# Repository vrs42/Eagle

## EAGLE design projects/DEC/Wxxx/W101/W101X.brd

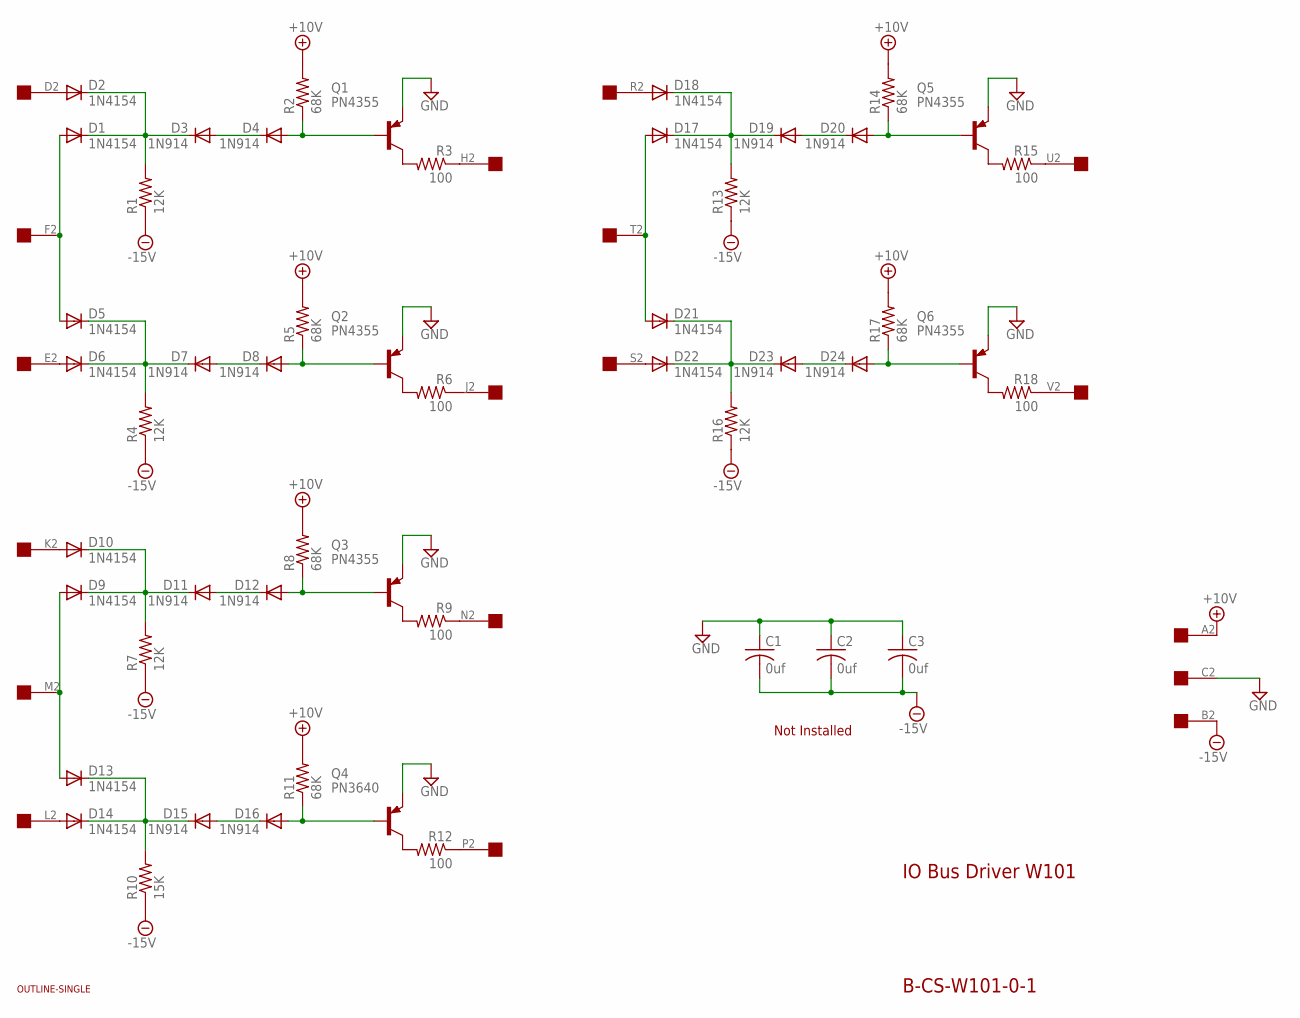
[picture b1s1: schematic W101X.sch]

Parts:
C1, C2, C3: 0uf; C050-025X075
D1, D2, D5, D6, D9, D10, D13, D14, D17, D18, D21, D22: 1N4154; DO35-10
D3, D4, D7, D8, D11, D12, D15, D16, D19, D20, D23, D24: 1N914; DO35-10
Q1, Q2, Q3, Q5, Q6: PN4355; TO39
Q4: PN3640; TO39
R1, R4, R7, R13, R16: 12K; 0207/10
R2, R5, R8, R11, R14, R17: 68K; 0207/10
R3, R6, R9, R12, R15, R18: 100; 0207/10
R10: 15K; 0207/10
U$1: OUTLINE-SINGLE; SINGLE
U$2: EDGE-1; EDGE-CON1

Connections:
+10V: R2.2, R5.2, R8.2, R11.2, R14.2, R17.2, U$2.A2
-15V: C1.2, C2.2, C3.2, R1.1, R4.1, R7.1, R10.1, R13.1, R16.1, U$2.B2
GND: C1.1, C2.1, C3.1, Q1.1 (E), Q2.1 (E), Q3.1 (E), Q4.1 (E), Q5.1 (E), Q6.1 (E), U$2.C2
unnamed: D2.A, U$2.D2
unnamed: D8.A, Q2.2 (B), R5.1
unnamed: R3.1, U$2.H2
unnamed: Q2.3 (C), R6.2
unnamed: D6.A, U$2.E2
unnamed: D5.C, D6.C, D7.C, R4.2
unnamed: D7.A, D8.C
unnamed: D12.A, Q3.2 (B), R8.1
unnamed: Q3.3 (C), R9.2
unnamed: D9.A, D13.A, U$2.M2
unnamed: D9.C, D10.C, D11.C, R7.2
unnamed: D11.A, D12.C
unnamed: R6.1, U$2.J2
unnamed: D10.A, U$2.K2
unnamed: R9.1, U$2.N2
unnamed: R12.1, U$2.P2
unnamed: D18.A, U$2.R2
unnamed: R15.1, U$2.U2
unnamed: D4.A, Q1.2 (B), R2.1
unnamed: Q1.3 (C), R3.2
unnamed: D1.A, D5.A, U$2.F2
unnamed: D1.C, D2.C, D3.C, R1.2
unnamed: D3.A, D4.C
unnamed: D16.A, Q4.2 (B), R11.1
unnamed: Q4.3 (C), R12.2
unnamed: D14.A, U$2.L2
unnamed: D13.C, D14.C, D15.C, R10.2
unnamed: D15.A, D16.C
unnamed: D20.A, Q5.2 (B), R14.1
unnamed: Q5.3 (C), R15.2
unnamed: D17.A, D21.A, U$2.T2
unnamed: D17.C, D18.C, D19.C, R13.2
unnamed: D19.A, D20.C
unnamed: D24.A, Q6.2 (B), R17.1
unnamed: Q6.3 (C), R18.2
unnamed: D22.A, U$2.S2
unnamed: D21.C, D22.C, D23.C, R16.2
unnamed: D23.A, D24.C
unnamed: R18.1, U$2.V2

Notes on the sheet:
IO Bus Driver W101
B-CS-W101-0-1
Not Installed

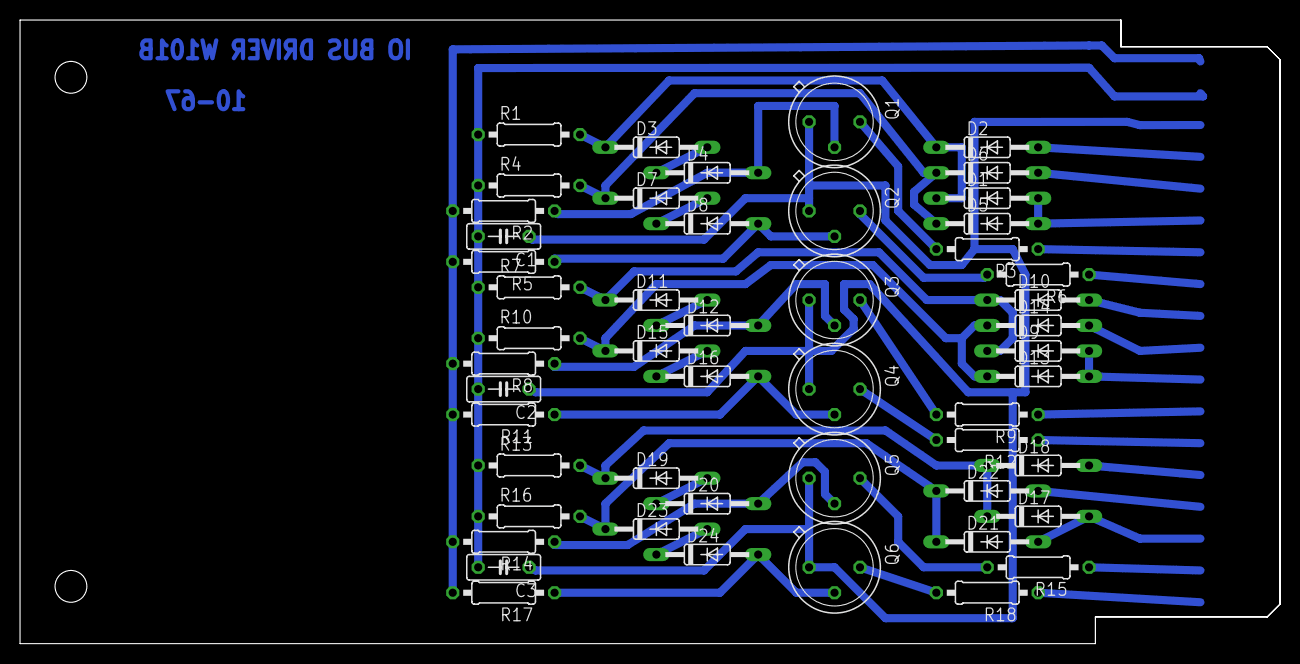
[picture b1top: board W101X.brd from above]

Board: 2 copper layers, 125.7 x 62.2 mm, 53 parts (0 on the bottom side), 42 nets.

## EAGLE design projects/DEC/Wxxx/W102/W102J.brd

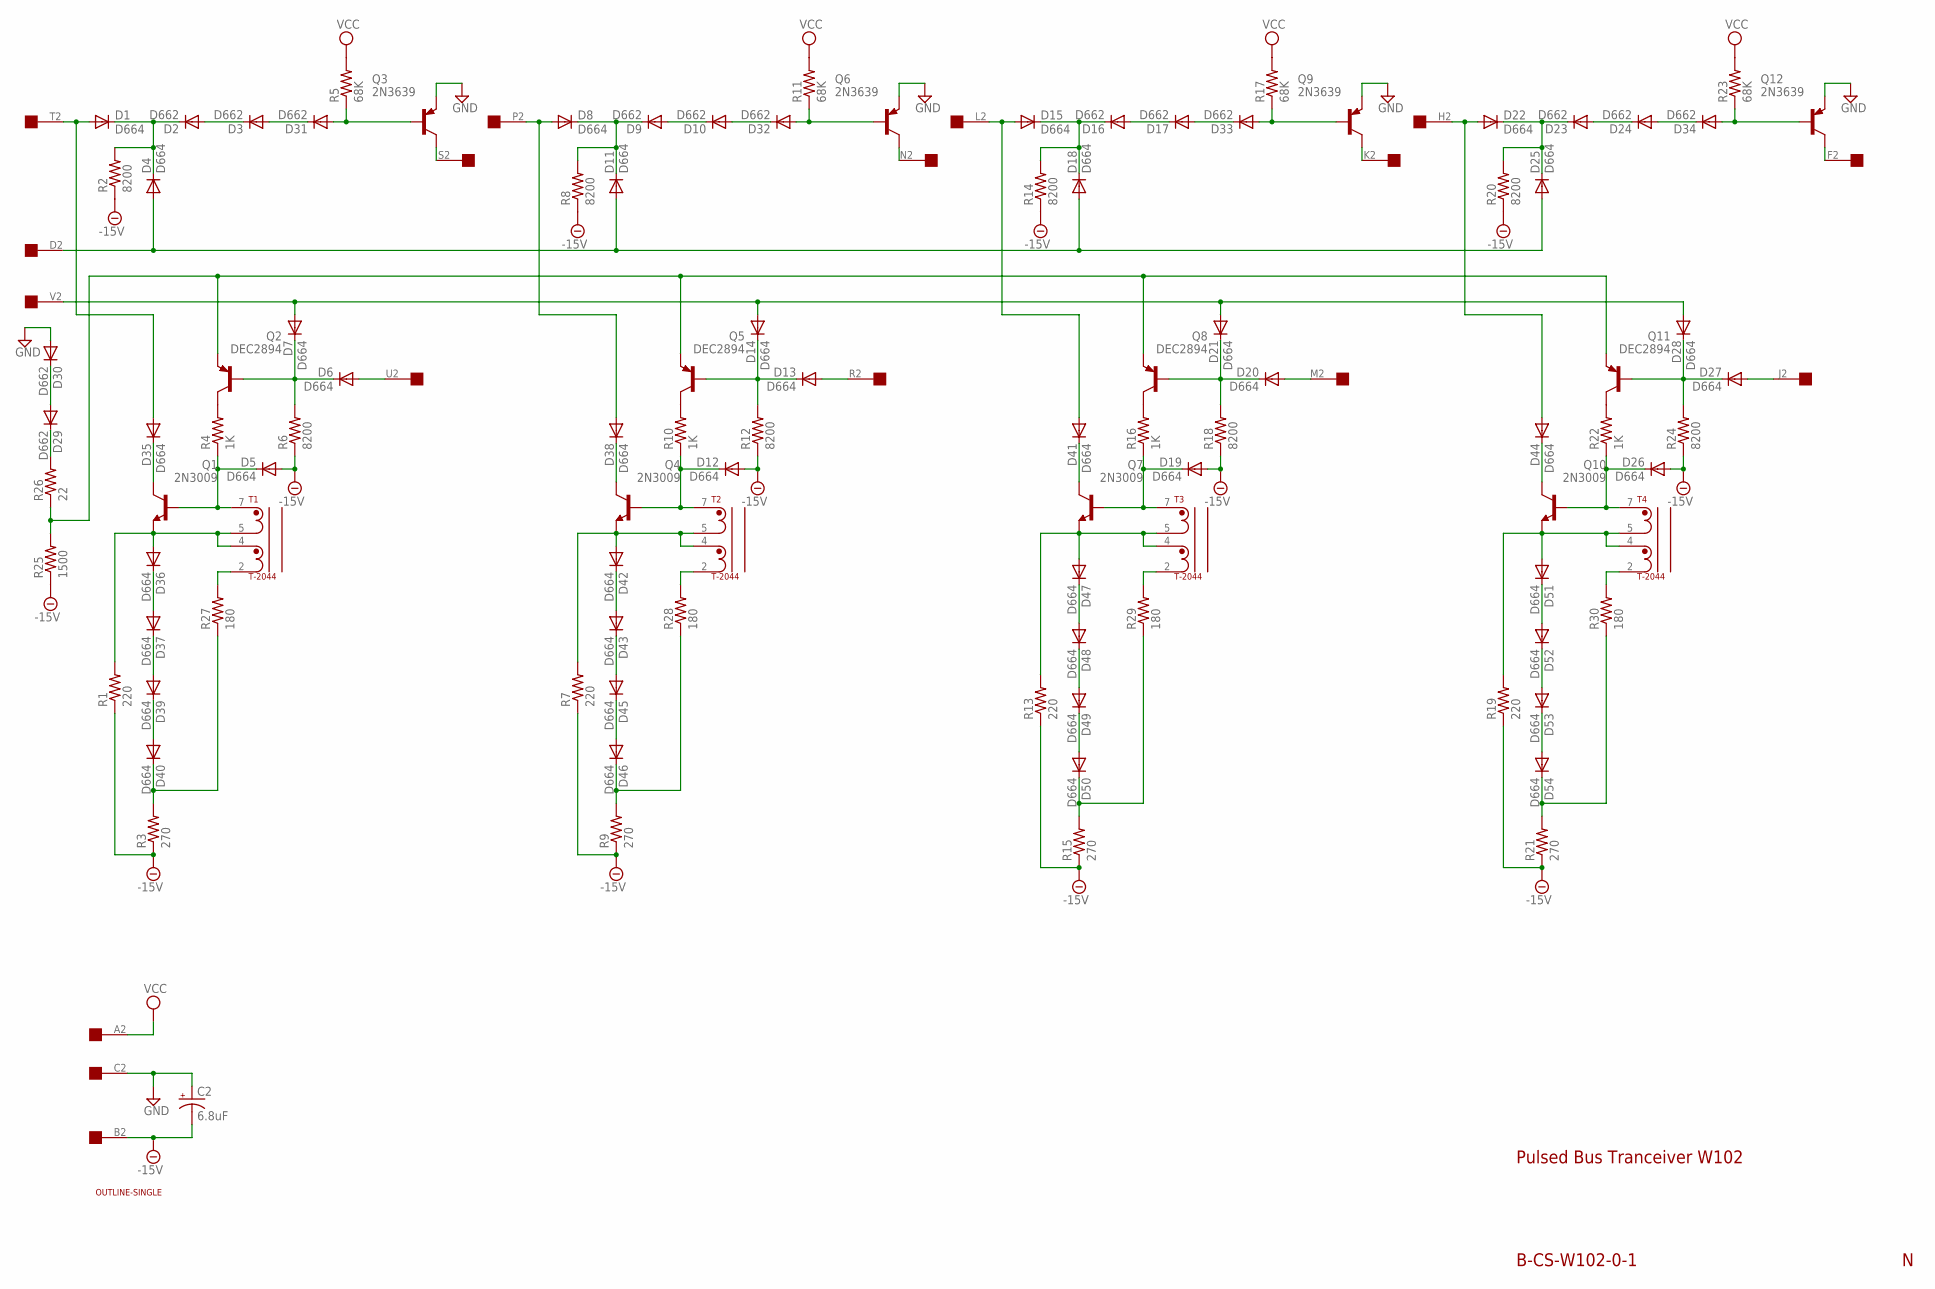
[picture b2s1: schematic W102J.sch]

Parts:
C2: 6.8uF; E15-5
D1, D4, D5, D6, D7, D8, D11, D12, D13, D14, D15, D18, D19, D20, D21, D22, D25, D26, D27, D28, D35, D36, D37, D38, D39, D40, D41, D42, D43, D44, D45, D46, D47, D48, D49, D50, D51, D52, D53, D54: D664; DO35-10
D2, D3, D9, D10, D16, D17, D23, D24, D29, D30, D31, D32, D33, D34: D662; DO35-10
Q1, Q4, Q7, Q10: 2N3009; TO5
Q2, Q5, Q8, Q11: DEC2894; TO5
Q3, Q6, Q9, Q12: 2N3639; TO5
R1, R7, R13, R19: 220; 0207/10
R2, R6, R8, R12, R14, R18, R20, R24: 8200; 0207/10
R3, R9, R15, R21: 270; 0207/10
R4, R10, R16, R22: 1K; 0207/10
R5, R11, R17, R23: 68K; 0207/10
R25: 1500; 0207/10
R26: 22; 0207/10
R27, R28, R29, R30: 180; 0207/10
T1, T2, T3, T4: T-2044; TRANSFORMER
U$1: OUTLINE-SINGLE; SINGLE
U$2: EDGE-1; EDGE-CON1

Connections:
-15V: C2.-, D5.A, D12.A, D19.A, D26.A, R1.1, R2.1, R3.1, R6.1, R7.1, R8.1, R9.1, R12.1, R13.1, R14.1, R15.1, R18.1, R19.1, R20.1, R21.1, R24.1, R25.1, U$2.B2
D2: D4.A, D11.A, D18.A, D25.A, U$2.D2
F2: Q12.3 (C), U$2.F2
GND: C2.+, D30.A, Q3.1 (E), Q6.1 (E), Q9.1 (E), Q12.1 (E), U$2.C2
H2: D22.A, D44.A, U$2.H2
J2: D27.A, U$2.J2
K2: Q9.3 (C), U$2.K2
L2: D15.A, D41.A, U$2.L2
M2: D20.A, U$2.M2
N2: Q6.3 (C), U$2.N2
unnamed: D1.C, D2.C, D4.C, R2.2
unnamed: D2.A, D3.C
unnamed: D3.A, D31.C
unnamed: D6.C, D7.C, Q2.2 (B), R6.2
unnamed: D8.C, D9.C, D11.C, R8.2
unnamed: D9.A, D10.C
unnamed: D10.A, D32.C
unnamed: D13.C, D14.C, Q5.2 (B), R12.2
unnamed: D15.C, D16.C, D18.C, R14.2
unnamed: D16.A, D17.C
unnamed: D17.A, D33.C
unnamed: D20.C, D21.C, Q8.2 (B), R18.2
unnamed: D22.C, D23.C, D25.C, R20.2
unnamed: D23.A, D24.C
unnamed: D24.A, D34.C
unnamed: D27.C, D28.C, Q11.2 (B), R24.2
unnamed: D5.C, Q1.2 (B), R4.1, T1.7 (2)
unnamed: D12.C, Q4.2 (B), R10.1, T2.7 (2)
unnamed: D19.C, Q7.2 (B), R16.1, T3.7 (2)
unnamed: D26.C, Q10.2 (B), R22.1, T4.7 (2)
unnamed: Q2.3 (C), R4.2
unnamed: Q8.3 (C), R16.2
unnamed: D36.A, Q1.1 (E), R1.2, T1.4 (1), T1.5
unnamed: D42.A, Q4.1 (E), R7.2, T2.4 (1), T2.5
unnamed: D47.A, Q7.1 (E), R13.2, T3.4 (1), T3.5
unnamed: D51.A, Q10.1 (E), R19.2, T4.4 (1), T4.5
unnamed: D35.C, Q1.3 (C)
unnamed: D39.C, D40.A
unnamed: D37.C, D39.A
unnamed: D36.C, D37.A
unnamed: R27.2, T1.2 (6)
unnamed: D40.C, R3.2, R27.1
unnamed: D31.A, Q3.2 (B), R5.1
unnamed: D42.C, D43.A
unnamed: D38.C, Q4.3 (C)
unnamed: D43.C, D45.A
unnamed: D32.A, Q6.2 (B), R11.1
unnamed: D33.A, Q9.2 (B), R17.1
unnamed: D34.A, Q12.2 (B), R23.1
unnamed: D45.C, D46.A
unnamed: Q2.1 (E), Q5.1 (E), Q8.1 (E), Q11.1 (E), R25.2, R26.1
unnamed: D29.C, R26.2
unnamed: D29.A, D30.C
unnamed: Q11.3 (C), R22.2
unnamed: Q5.3 (C), R10.2
unnamed: R28.2, T2.2 (6)
unnamed: D41.C, Q7.3 (C)
unnamed: D47.C, D48.A
unnamed: D48.C, D49.A
unnamed: D49.C, D50.A
unnamed: R29.2, T3.2 (6)
unnamed: D46.C, R9.2, R28.1
unnamed: D44.C, Q10.3 (C)
unnamed: D53.C, D54.A
unnamed: D50.C, R15.2, R29.1
unnamed: D52.C, D53.A
unnamed: D51.C, D52.A
unnamed: R30.2, T4.2 (6)
unnamed: D54.C, R21.2, R30.1
P2: D8.A, D38.A, U$2.P2
R2: D13.A, U$2.R2
S2: Q3.3 (C), U$2.S2
T2: D1.A, D35.A, U$2.T2
U2: D6.A, U$2.U2
V2: D7.A, D14.A, D21.A, D28.A, U$2.V2
VCC: R5.2, R11.2, R17.2, R23.2, U$2.A2

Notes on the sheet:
Pulsed Bus Tranceiver W102
B-CS-W102-0-1

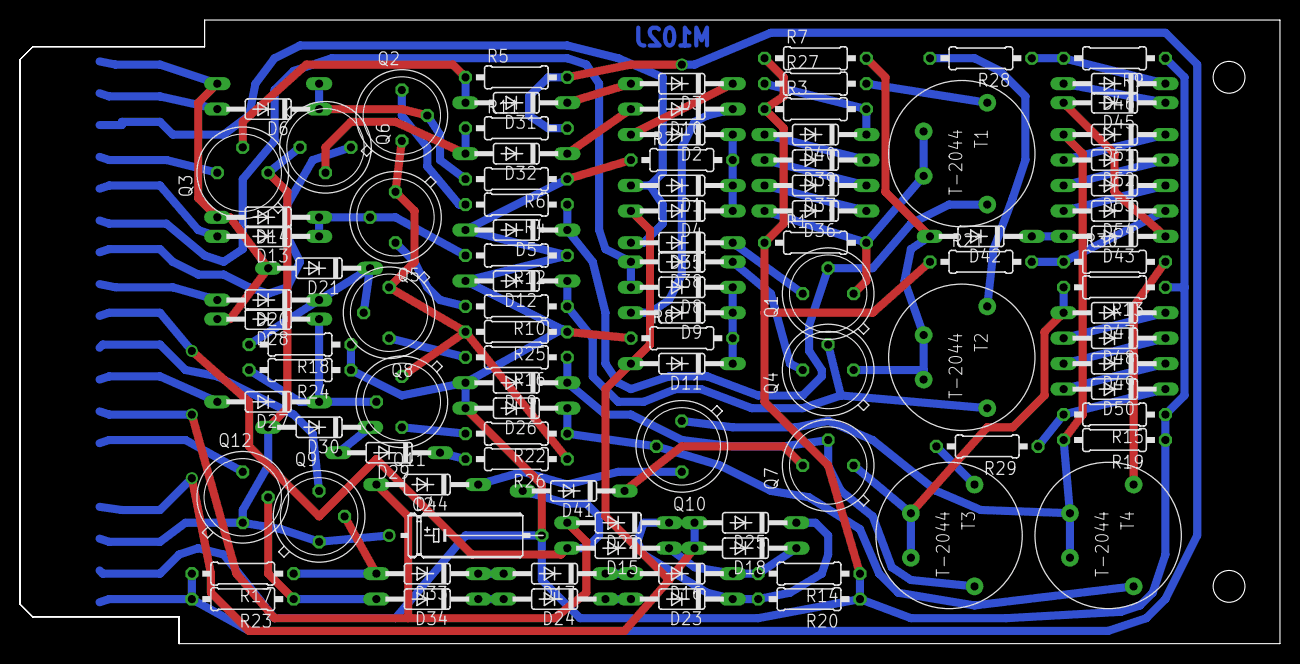
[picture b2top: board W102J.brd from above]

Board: 2 copper layers, 125.7 x 62.2 mm, 103 parts (1 on the bottom side), 76 nets.

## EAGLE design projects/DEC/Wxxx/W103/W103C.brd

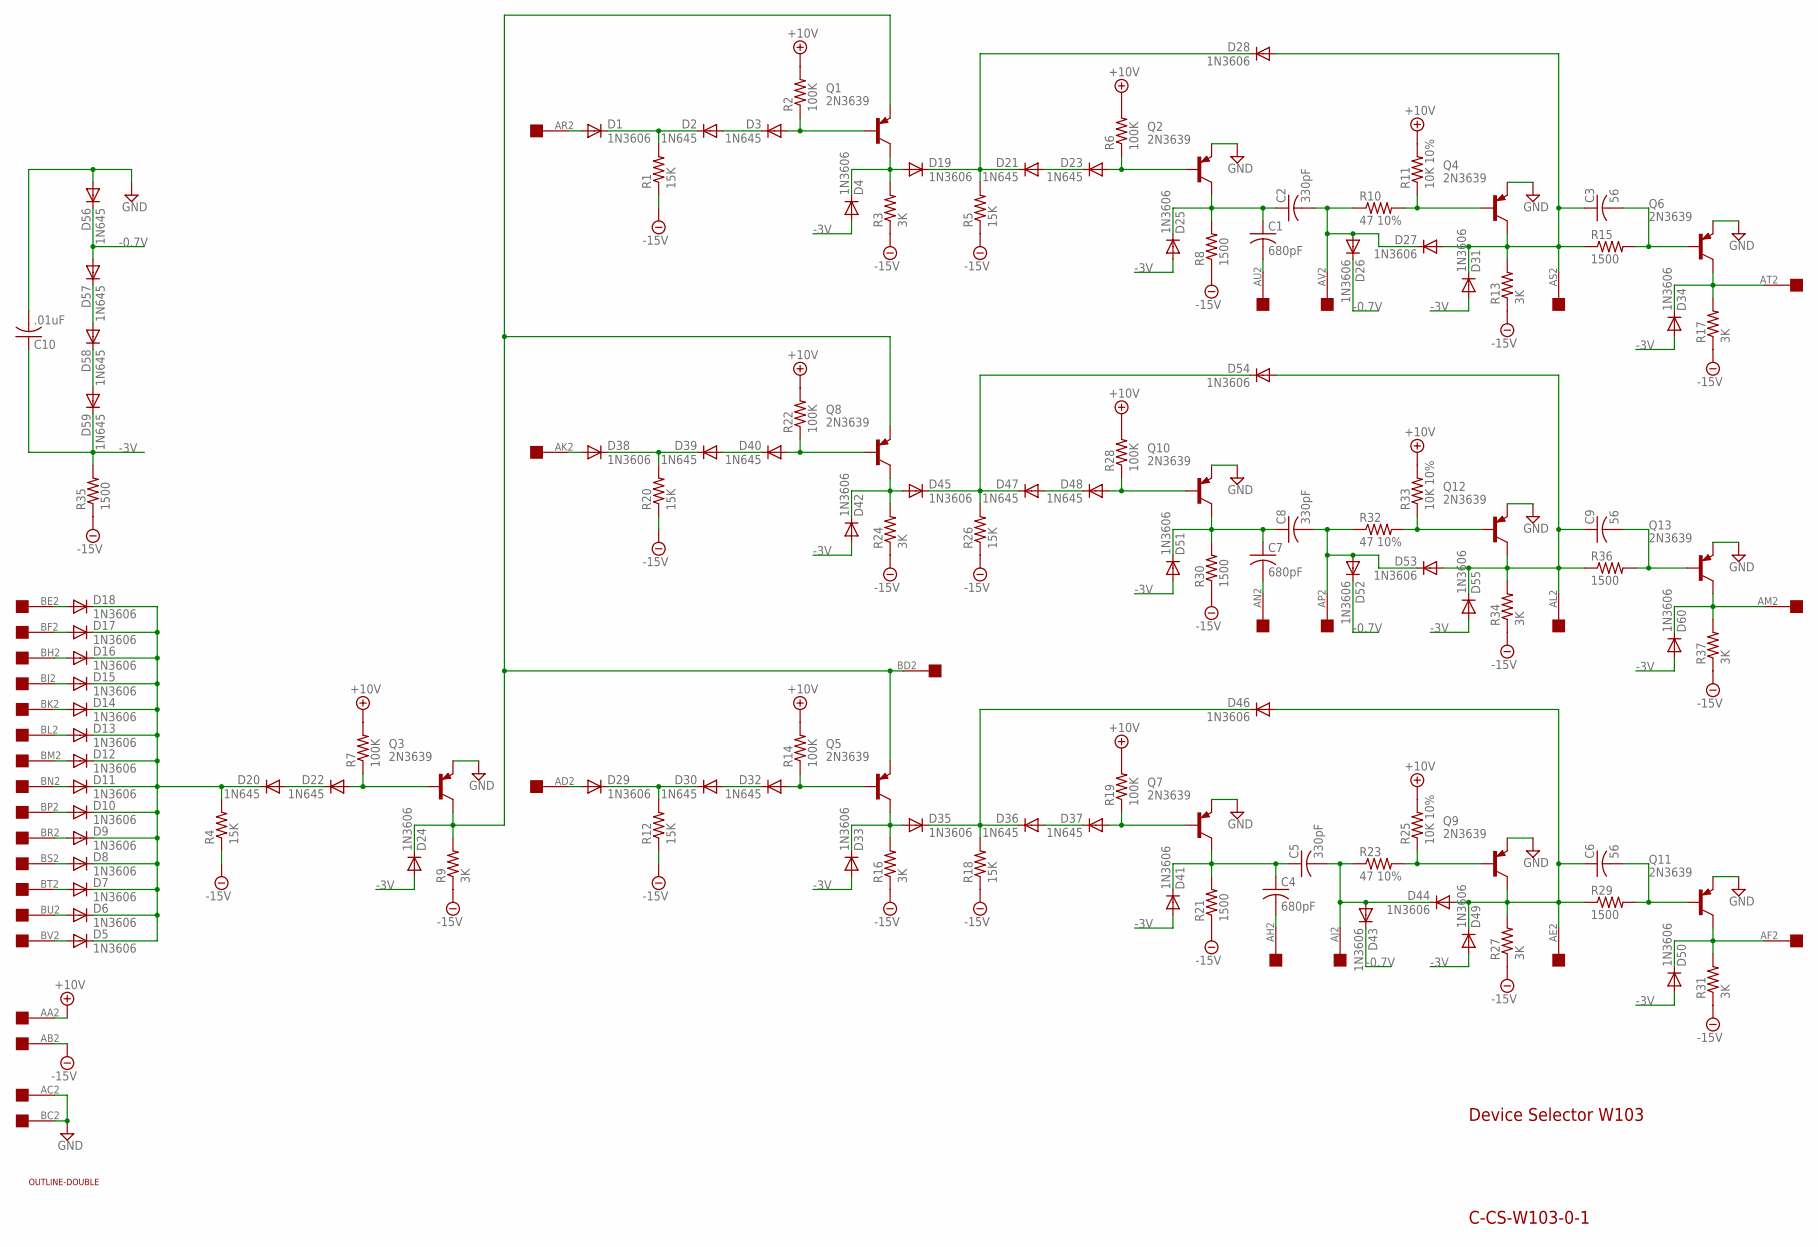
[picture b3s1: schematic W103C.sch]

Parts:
C1, C4, C7: 680pF; C075-032X103
C2, C5, C8: 330pF; C075-032X103
C3, C6, C9: 56; C075-032X103
C10: .01uF; C075-032X103
D1, D4, D5, D6, D7, D8, D9, D10, D11, D12, D13, D14, D15, D16, D17, D18, D19, D24, D25, D26, D27, D28, D29, D31, D33, D34, D35, D38, D41, D42, D43, D44, D45, D46, D49, D50, D51, D52, D53, D54, D55, D60: 1N3606; DO35-10
D2, D3, D20, D21, D22, D23, D30, D32, D36, D37, D39, D40, D47, D48, D56, D57, D58, D59: 1N645; DO35-10
Q1, Q2, Q3, Q4, Q5, Q6, Q7, Q8, Q9, Q10, Q11, Q12, Q13: 2N3639; TO39
R1, R4, R5, R12, R18, R20, R26: 15K; 0207/10
R2, R6, R7, R14, R19, R22, R28: 100K; 0207/10
R3, R9, R13, R16, R17, R24, R27, R31, R34, R37: 3K; 0207/10
R8, R15, R21, R29, R30, R35, R36: 1500; 0207/10
R10, R23, R32: 47 10%; 0207/10
R11, R25, R33: 10K 10%; 0207/10
U$1: OUTLINE-DOUBLE; DOUBLE
U$2: DOUBLE; EDGE-CON4

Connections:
+10V: R2.2, R6.2, R7.2, R11.2, R14.2, R19.2, R22.2, R25.2, R28.2, R33.2, U$2.AA2
-0.7V: D26.C, D43.C, D52.C, D56.C, D57.A
-3V: C10.1, D4.A, D24.A, D25.A, D31.A, D33.A, D34.A, D41.A, D42.A, D49.A, D50.A, D51.A, D55.A, D59.C, D60.A, R35.2
-15V: R1.1, R3.1, R4.1, R5.1, R8.1, R9.1, R12.1, R13.1, R16.1, R17.1, R18.1, R20.1, R21.1, R24.1, R26.1, R27.1, R30.1, R31.1, R34.1, R35.1, R37.1, U$2.AB2
GND: C10.2, D56.A, Q2.1 (E), Q3.1 (E), Q4.1 (E), Q6.1 (E), Q7.1 (E), Q9.1 (E), Q10.1 (E), Q11.1 (E), Q12.1 (E), Q13.1 (E), U$2.AC2, U$2.BC2
unnamed: D14.A, U$2.BK2
unnamed: D15.A, U$2.BJ2
unnamed: D16.A, U$2.BH2
unnamed: D17.A, U$2.BF2
unnamed: D18.A, U$2.BE2
unnamed: D13.A, U$2.BL2
unnamed: D5.A, U$2.BV2
unnamed: D6.A, U$2.BU2
unnamed: D7.A, U$2.BT2
unnamed: D8.A, U$2.BS2
unnamed: D9.A, U$2.BR2
unnamed: D10.A, U$2.BP2
unnamed: D11.A, U$2.BN2
unnamed: D12.A, U$2.BM2
unnamed: D5.C, D6.C, D7.C, D8.C, D9.C, D10.C, D11.C, D12.C, D13.C, D14.C, D15.C, D16.C, D17.C, D18.C, D20.C, R4.2
unnamed: D20.A, D22.C
unnamed: D22.A, Q3.2 (B), R7.1
unnamed: D24.C, Q1.1 (E), Q3.3 (C), Q5.1 (E), Q8.1 (E), R9.2, U$2.BD2
unnamed: D29.A, U$2.AD2
unnamed: D29.C, D30.C, R12.2
unnamed: D30.A, D32.C
unnamed: D32.A, Q5.2 (B), R14.1
unnamed: D33.C, D35.A, Q5.3 (C), R16.2
unnamed: D1.A, U$2.AR2
unnamed: D35.C, D36.C, D46.C, R18.2
unnamed: D36.A, D37.C
unnamed: D37.A, Q7.2 (B), R19.1
unnamed: C4.1, C5.1, D41.C, Q7.3 (C), R21.2
unnamed: C4.2, U$2.AH2
unnamed: C5.2, D43.A, D44.C, R23.1, U$2.AJ2
unnamed: Q9.2 (B), R23.2, R25.1
unnamed: C6.1, D44.A, D46.A, D49.C, Q9.3 (C), R27.2, R29.1, U$2.AE2
unnamed: C6.2, Q11.2 (B), R29.2
unnamed: D50.C, Q11.3 (C), R31.2, U$2.AF2
unnamed: D1.C, D2.C, R1.2
unnamed: D2.A, D3.C
unnamed: D3.A, Q1.2 (B), R2.1
unnamed: D4.C, D19.A, Q1.3 (C), R3.2
unnamed: D19.C, D21.C, D28.C, R5.2
unnamed: D21.A, D23.C
unnamed: D23.A, Q2.2 (B), R6.1
unnamed: C1.1, C2.1, D25.C, Q2.3 (C), R8.2
unnamed: D38.A, U$2.AK2
unnamed: C1.2, U$2.AU2
unnamed: C2.2, D26.A, D27.C, R10.1, U$2.AV2
unnamed: Q4.2 (B), R10.2, R11.1
unnamed: C3.1, D27.A, D28.A, D31.C, Q4.3 (C), R13.2, R15.1, U$2.AS2
unnamed: C3.2, Q6.2 (B), R15.2
unnamed: D34.C, Q6.3 (C), R17.2, U$2.AT2
unnamed: D38.C, D39.C, R20.2
unnamed: D39.A, D40.C
unnamed: D40.A, Q8.2 (B), R22.1
unnamed: D42.C, D45.A, Q8.3 (C), R24.2
unnamed: D45.C, D47.C, D54.C, R26.2
unnamed: D47.A, D48.C
unnamed: D48.A, Q10.2 (B), R28.1
unnamed: C7.1, C8.1, D51.C, Q10.3 (C), R30.2
unnamed: C7.2, U$2.AN2
unnamed: C8.2, D52.A, D53.C, R32.1, U$2.AP2
unnamed: Q12.2 (B), R32.2, R33.1
unnamed: C9.1, D53.A, D54.A, D55.C, Q12.3 (C), R34.2, R36.1, U$2.AL2
unnamed: C9.2, Q13.2 (B), R36.2
unnamed: D60.C, Q13.3 (C), R37.2, U$2.AM2
unnamed: D58.C, D59.A
unnamed: D57.C, D58.A

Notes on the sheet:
Device Selector W103
C-CS-W103-0-1

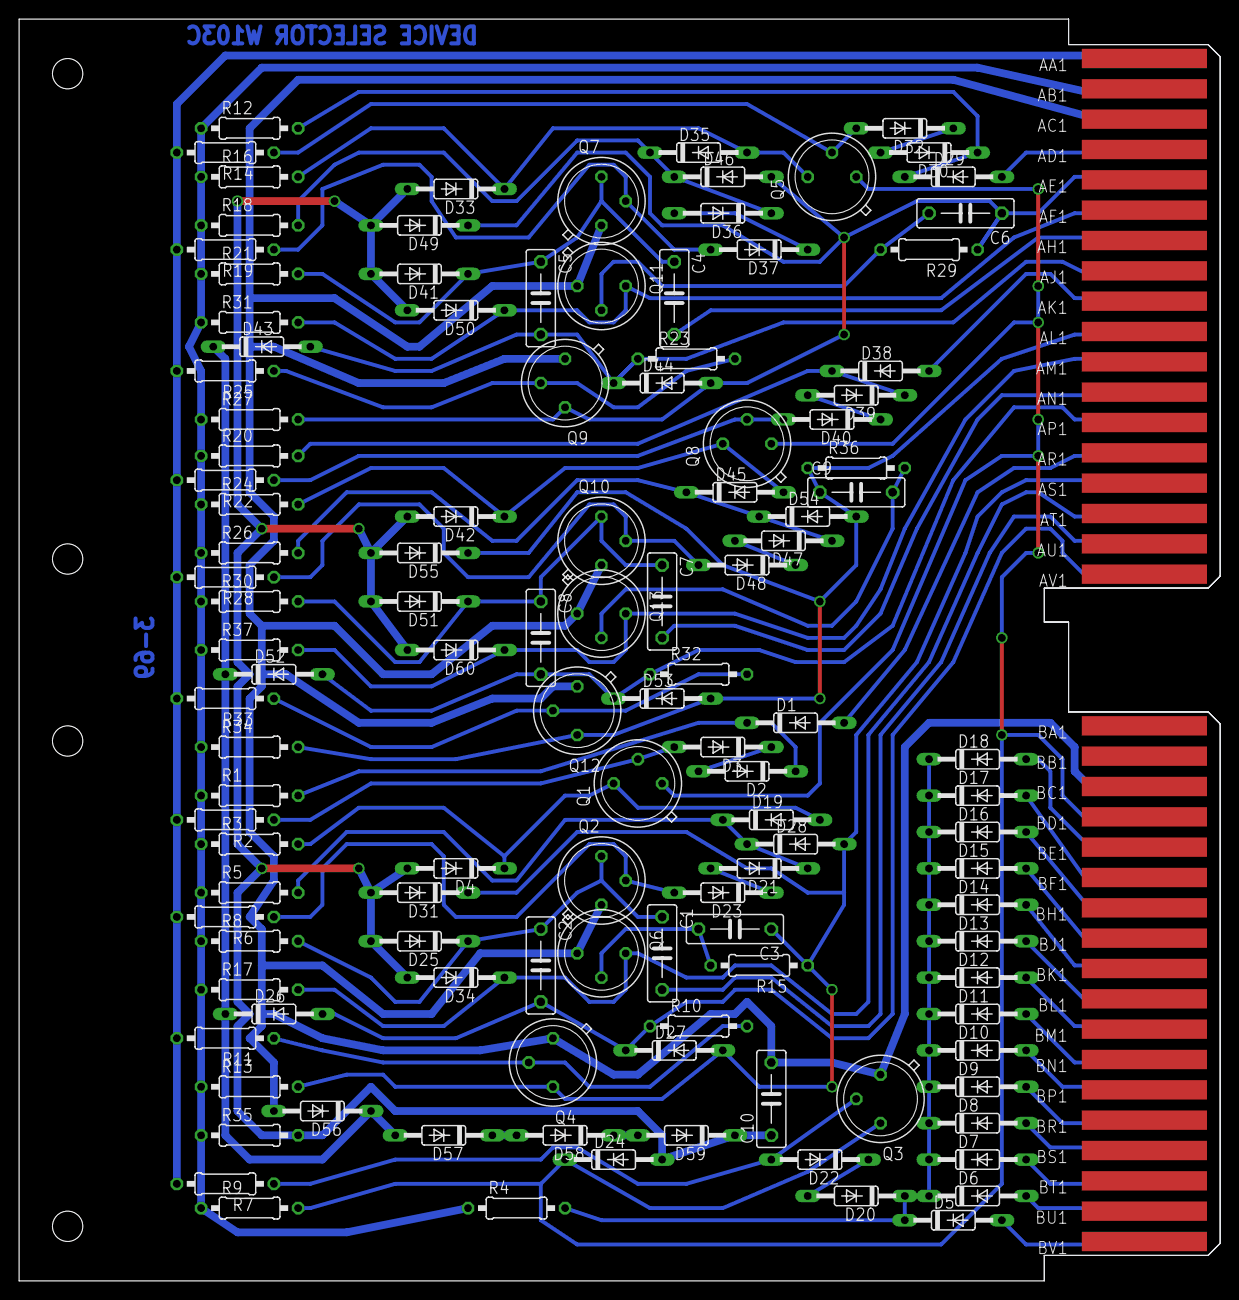
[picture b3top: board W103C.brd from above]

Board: 2 copper layers, 125.7 x 132.1 mm, 122 parts (0 on the bottom side), 70 nets.

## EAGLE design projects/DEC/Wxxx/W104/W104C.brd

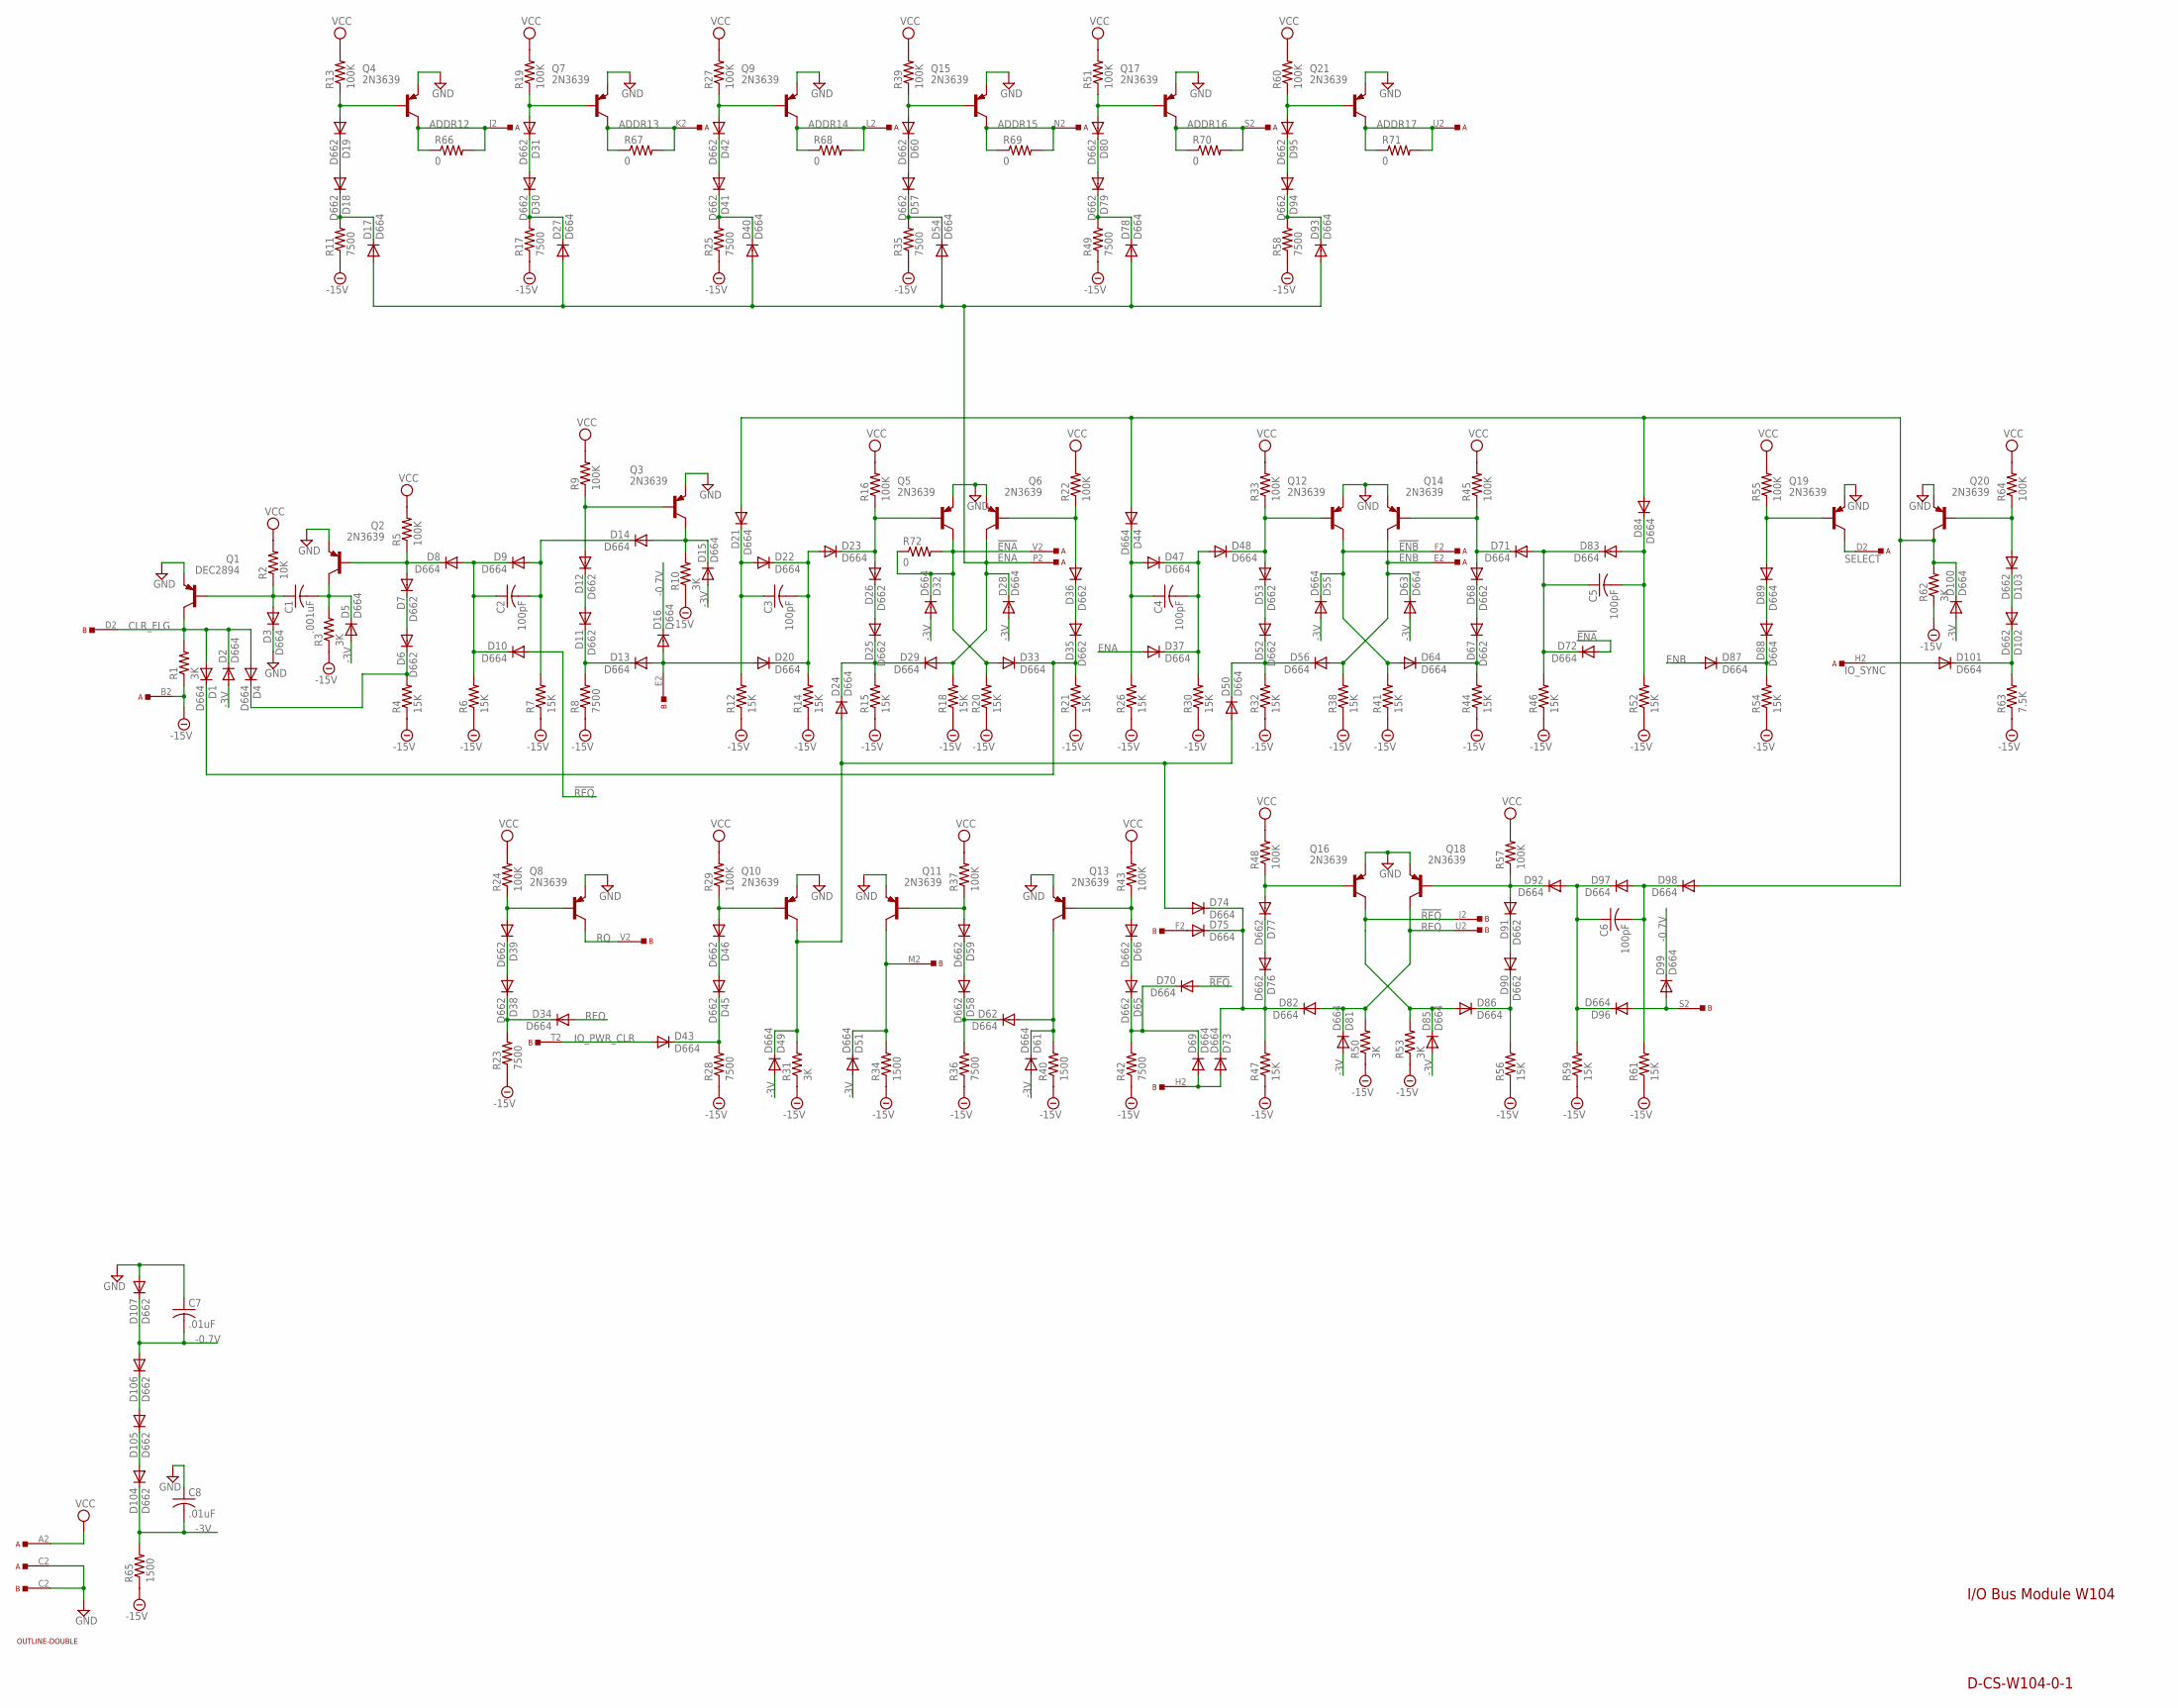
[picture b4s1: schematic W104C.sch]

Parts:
A: SS-TOP; EDGE-CON1
B: SS-TOP; EDGE-CON1
C1: .001uF; C063-025X075
C2, C3, C4, C5, C6: 100pF; C150-054X183
C7, C8: .01uF; C063-025X075
D1, D2, D3, D4, D5, D8, D9, D10, D13, D14, D15, D16, D17, D20, D21, D22, D23, D24, D27, D28, D29, D32, D33, D34, D37, D40, D43, D44, D47, D48, D49, D50, D51, D54, D55, D56, D61, D62, D63, D64, D69, D70, D71, D72, D73, D74, D75, D78, D81, D82, D83, D84, D85, D86, D87, D88, D89, D92, D93, D96, D97, D98, D99, D100, D101: D664; DO35-10
D6, D7, D11, D12, D18, D19, D25, D26, D30, D31, D35, D36, D38, D39, D41, D42, D45, D46, D52, D53, D57, D58, D59, D60, D65, D66, D67, D68, D76, D77, D79, D80, D90, D91, D94, D95, D102, D103, D104, D105, D106, D107: D662; DO35-10
Q1: DEC2894; TO5
Q2, Q3, Q4, Q5, Q6, Q7, Q8, Q9, Q10, Q11, Q12, Q13, Q14, Q15, Q16, Q17, Q18, Q19, Q20, Q21: 2N3639; TO5
R1, R3, R10, R31, R50, R53, R62: 3K; 0207/10
R2: 10K; 0207/10
R4, R6, R7, R12, R14, R15, R18, R20, R21, R26, R30, R32, R38, R41, R44, R46, R47, R52, R54, R56, R59, R61: 15K; 0207/10
R5, R9, R13, R16, R19, R22, R24, R27, R29, R33, R37, R39, R43, R45, R48, R51, R55, R57, R60, R64: 100K; 0207/10
R8, R11, R17, R23, R25, R28, R35, R36, R42, R49, R58: 7500; 0207/10
R34, R40, R65: 1500; 0207/10
R63: 7.5K; 0207/10
R66, R67, R68, R69, R70, R71, R72: 0; 0207/10
U$1: OUTLINE-DOUBLE; DOUBLE

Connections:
!ENA: A.V2, D32.C, D33.A, D72.A, Q5.3 (C), R20.2, R72.1, R72.2
!ENB: A.F2, D55.C, D64.A, Q12.3 (C), R41.2
!REQ: B.J2, D10.A, D70.A, D85.C, D86.A, Q16.3 (C), R53.2
-0.7V: C7.2, D16.C, D99.C, D106.A, D107.C
-3V: C8.2, D2.A, D5.A, D15.A, D28.A, D32.A, D49.A, D51.A, D55.A, D61.A, D63.A, D81.A, D85.A, D100.A, D104.C, R65.2
-15V: A.B2, R1.1, R3.1, R4.1, R6.1, R7.1, R8.1, R10.1, R11.1, R12.1, R14.1, R15.1, R17.1, R18.1, R20.1, R21.1, R23.1, R25.1, R26.1, R28.1, R30.1, R31.1, R32.1, R34.1, R35.1, R36.1, R38.1, R40.1, R41.1, R42.1, R44.1, R46.1, R47.1, R49.1, R50.1, R52.1, R53.1, R54.1, R56.1, R58.1, R59.1, R61.1, R62.1, R63.1, R65.1
ADDR12: A.J2, Q4.3 (C), R66.1, R66.2
ADDR13: A.K2, Q7.3 (C), R67.1, R67.2
ADDR14: A.L2, Q9.3 (C), R68.1, R68.2
ADDR15: A.N2, Q15.3 (C), R69.1, R69.2
ADDR16: A.S2, Q17.3 (C), R70.1, R70.2
ADDR17: A.U2, Q21.3 (C), R71.1, R71.2
CLR_FLG: B.D2, D1.A, D2.C, D4.A, Q1.3 (C), R1.2
ENA: A.P2, D17.A, D27.A, D28.C, D29.A, D37.A, D40.A, D54.A, D78.A, D93.A, Q6.3 (C), R18.2
ENB: A.E2, D56.A, D63.C, D87.A, Q14.3 (C), R38.2
GND: A.C2, B.C2, C7.1, C8.1, D3.C, D107.A, Q1.1 (E), Q2.1 (E), Q3.1 (E), Q4.1 (E), Q5.1 (E), Q6.1 (E), Q7.1 (E), Q8.1 (E), Q9.1 (E), Q10.1 (E), Q11.1 (E), Q12.1 (E), Q13.1 (E), Q14.1 (E), Q15.1 (E), Q16.1 (E), Q17.1 (E), Q18.1 (E), Q19.1 (E), Q20.1 (E), Q21.1 (E)
IO_PWR_CLR: B.T2, D43.A
IO_SYNC: A.H2, D101.A
unnamed: D19.A, Q4.2 (B), R13.1
unnamed: C1.1, D3.A, Q1.2 (B), R2.1
unnamed: D1.C, D33.C, D35.C, R21.2
unnamed: D4.C, D6.C, R4.2
unnamed: C1.2, D5.C, Q2.3 (C), R3.2
unnamed: D7.A, D8.C, Q2.2 (B), R5.1
unnamed: D6.A, D7.C
unnamed: C2.2, D9.A, D14.C, R7.2
unnamed: C2.1, D8.A, D9.C, D10.C, R6.2
unnamed: C6.1, D92.A, D96.C, D97.C, R59.2
unnamed: D11.A, D12.C
unnamed: D11.C, D13.C, R8.2
unnamed: D12.A, Q3.2 (B), R9.1
unnamed: D14.A, D15.C, Q3.3 (C), R10.2
unnamed: B.E2, D13.A, D16.A, D20.A
unnamed: D60.A, Q15.2 (B), R39.1
unnamed: C3.2, D20.C, D22.C, D23.A, R14.2
unnamed: D17.C, D18.C, R11.2
unnamed: D18.A, D19.C
unnamed: D36.A, Q6.2 (B), R22.1
unnamed: D27.C, D30.C, R17.2
unnamed: D30.A, D31.C
unnamed: D31.A, Q7.2 (B), R19.1
unnamed: D42.A, Q9.2 (B), R27.1
unnamed: D41.A, D42.C
unnamed: D40.C, D41.C, R25.2
unnamed: D57.A, D60.C
unnamed: D54.C, D57.C, R35.2
unnamed: D80.A, Q17.2 (B), R51.1
unnamed: D79.A, D80.C
unnamed: D78.C, D79.C, R49.2
unnamed: D95.A, Q21.2 (B), R60.1
unnamed: D94.A, D95.C
unnamed: D93.C, D94.C, R58.2
unnamed: C3.1, D21.C, D22.A, R12.2
unnamed: D23.C, D26.A, Q5.2 (B), R16.1
unnamed: D24.C, D25.C, D29.C, R15.2
unnamed: D21.A, D44.A, D84.A, D98.A, D100.C, Q20.3 (C), R62.2
unnamed: D25.A, D26.C
unnamed: D24.A, D49.C, D50.A, D74.A, Q10.3 (C), R31.2
unnamed: D39.A, Q8.2 (B), R24.1
unnamed: D38.A, D39.C
unnamed: D34.C, D38.C, R23.2
unnamed: D43.C, D45.C, R28.2
unnamed: D45.A, D46.C
unnamed: D46.A, Q10.2 (B), R29.1
unnamed: B.M2, D51.C, Q11.3 (C), R34.2
unnamed: D59.A, Q11.2 (B), R37.1
unnamed: D58.A, D59.C
unnamed: D58.C, D62.C, R36.2
unnamed: D61.C, D62.A, Q13.3 (C), R40.2
unnamed: D66.A, Q13.2 (B), R43.1
unnamed: D65.A, D66.C
unnamed: D65.C, D69.C, D70.C, R42.2
unnamed: B.H2, D69.A, D73.A
unnamed: B.F2, D75.A
unnamed: D77.A, Q16.2 (B), R48.1
unnamed: D76.A, D77.C
unnamed: D73.C, D74.C, D75.C, D76.C, D82.C, R47.2
unnamed: D91.A, D92.C, Q18.2 (B), R57.1
unnamed: D90.A, D91.C
unnamed: D105.A, D106.C
unnamed: D68.A, D71.C, Q14.2 (B), R45.1
unnamed: D35.A, D36.C
unnamed: D104.A, D105.C
unnamed: D102.A, D103.C
unnamed: D101.C, D102.C, R63.2
unnamed: D103.A, Q20.2 (B), R64.1
unnamed: B.S2, D96.A, D99.A
unnamed: D86.C, D90.C, R56.2
unnamed: D48.C, D53.A, Q12.2 (B), R33.1
unnamed: C4.1, D44.C, D47.A, R26.2
unnamed: C4.2, D37.C, D47.C, D48.A, R30.2
unnamed: D67.A, D68.C
unnamed: D52.A, D53.C
unnamed: D50.C, D52.C, D56.C, R32.2
unnamed: D64.C, D67.C, R44.2
unnamed: C5.1, D71.A, D72.C, D83.C, R46.2
unnamed: D89.A, Q19.2 (B), R55.1
unnamed: C5.2, D83.A, D84.C, R52.2
unnamed: D87.C, D88.C, R54.2
unnamed: D88.A, D89.C
unnamed: C6.2, D97.A, D98.C, R61.2
REQ: B.U2, D34.A, D81.C, D82.A, Q18.3 (C), R50.2
RQ: B.V2, Q8.3 (C)
SELECT: A.D2, Q19.3 (C)
VCC: A.A2, R2.2, R5.2, R9.2, R13.2, R16.2, R19.2, R22.2, R24.2, R27.2, R29.2, R33.2, R37.2, R39.2, R43.2, R45.2, R48.2, R51.2, R55.2, R57.2, R60.2, R64.2

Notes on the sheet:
I/O Bus Module W104
D-CS-W104-0-1
